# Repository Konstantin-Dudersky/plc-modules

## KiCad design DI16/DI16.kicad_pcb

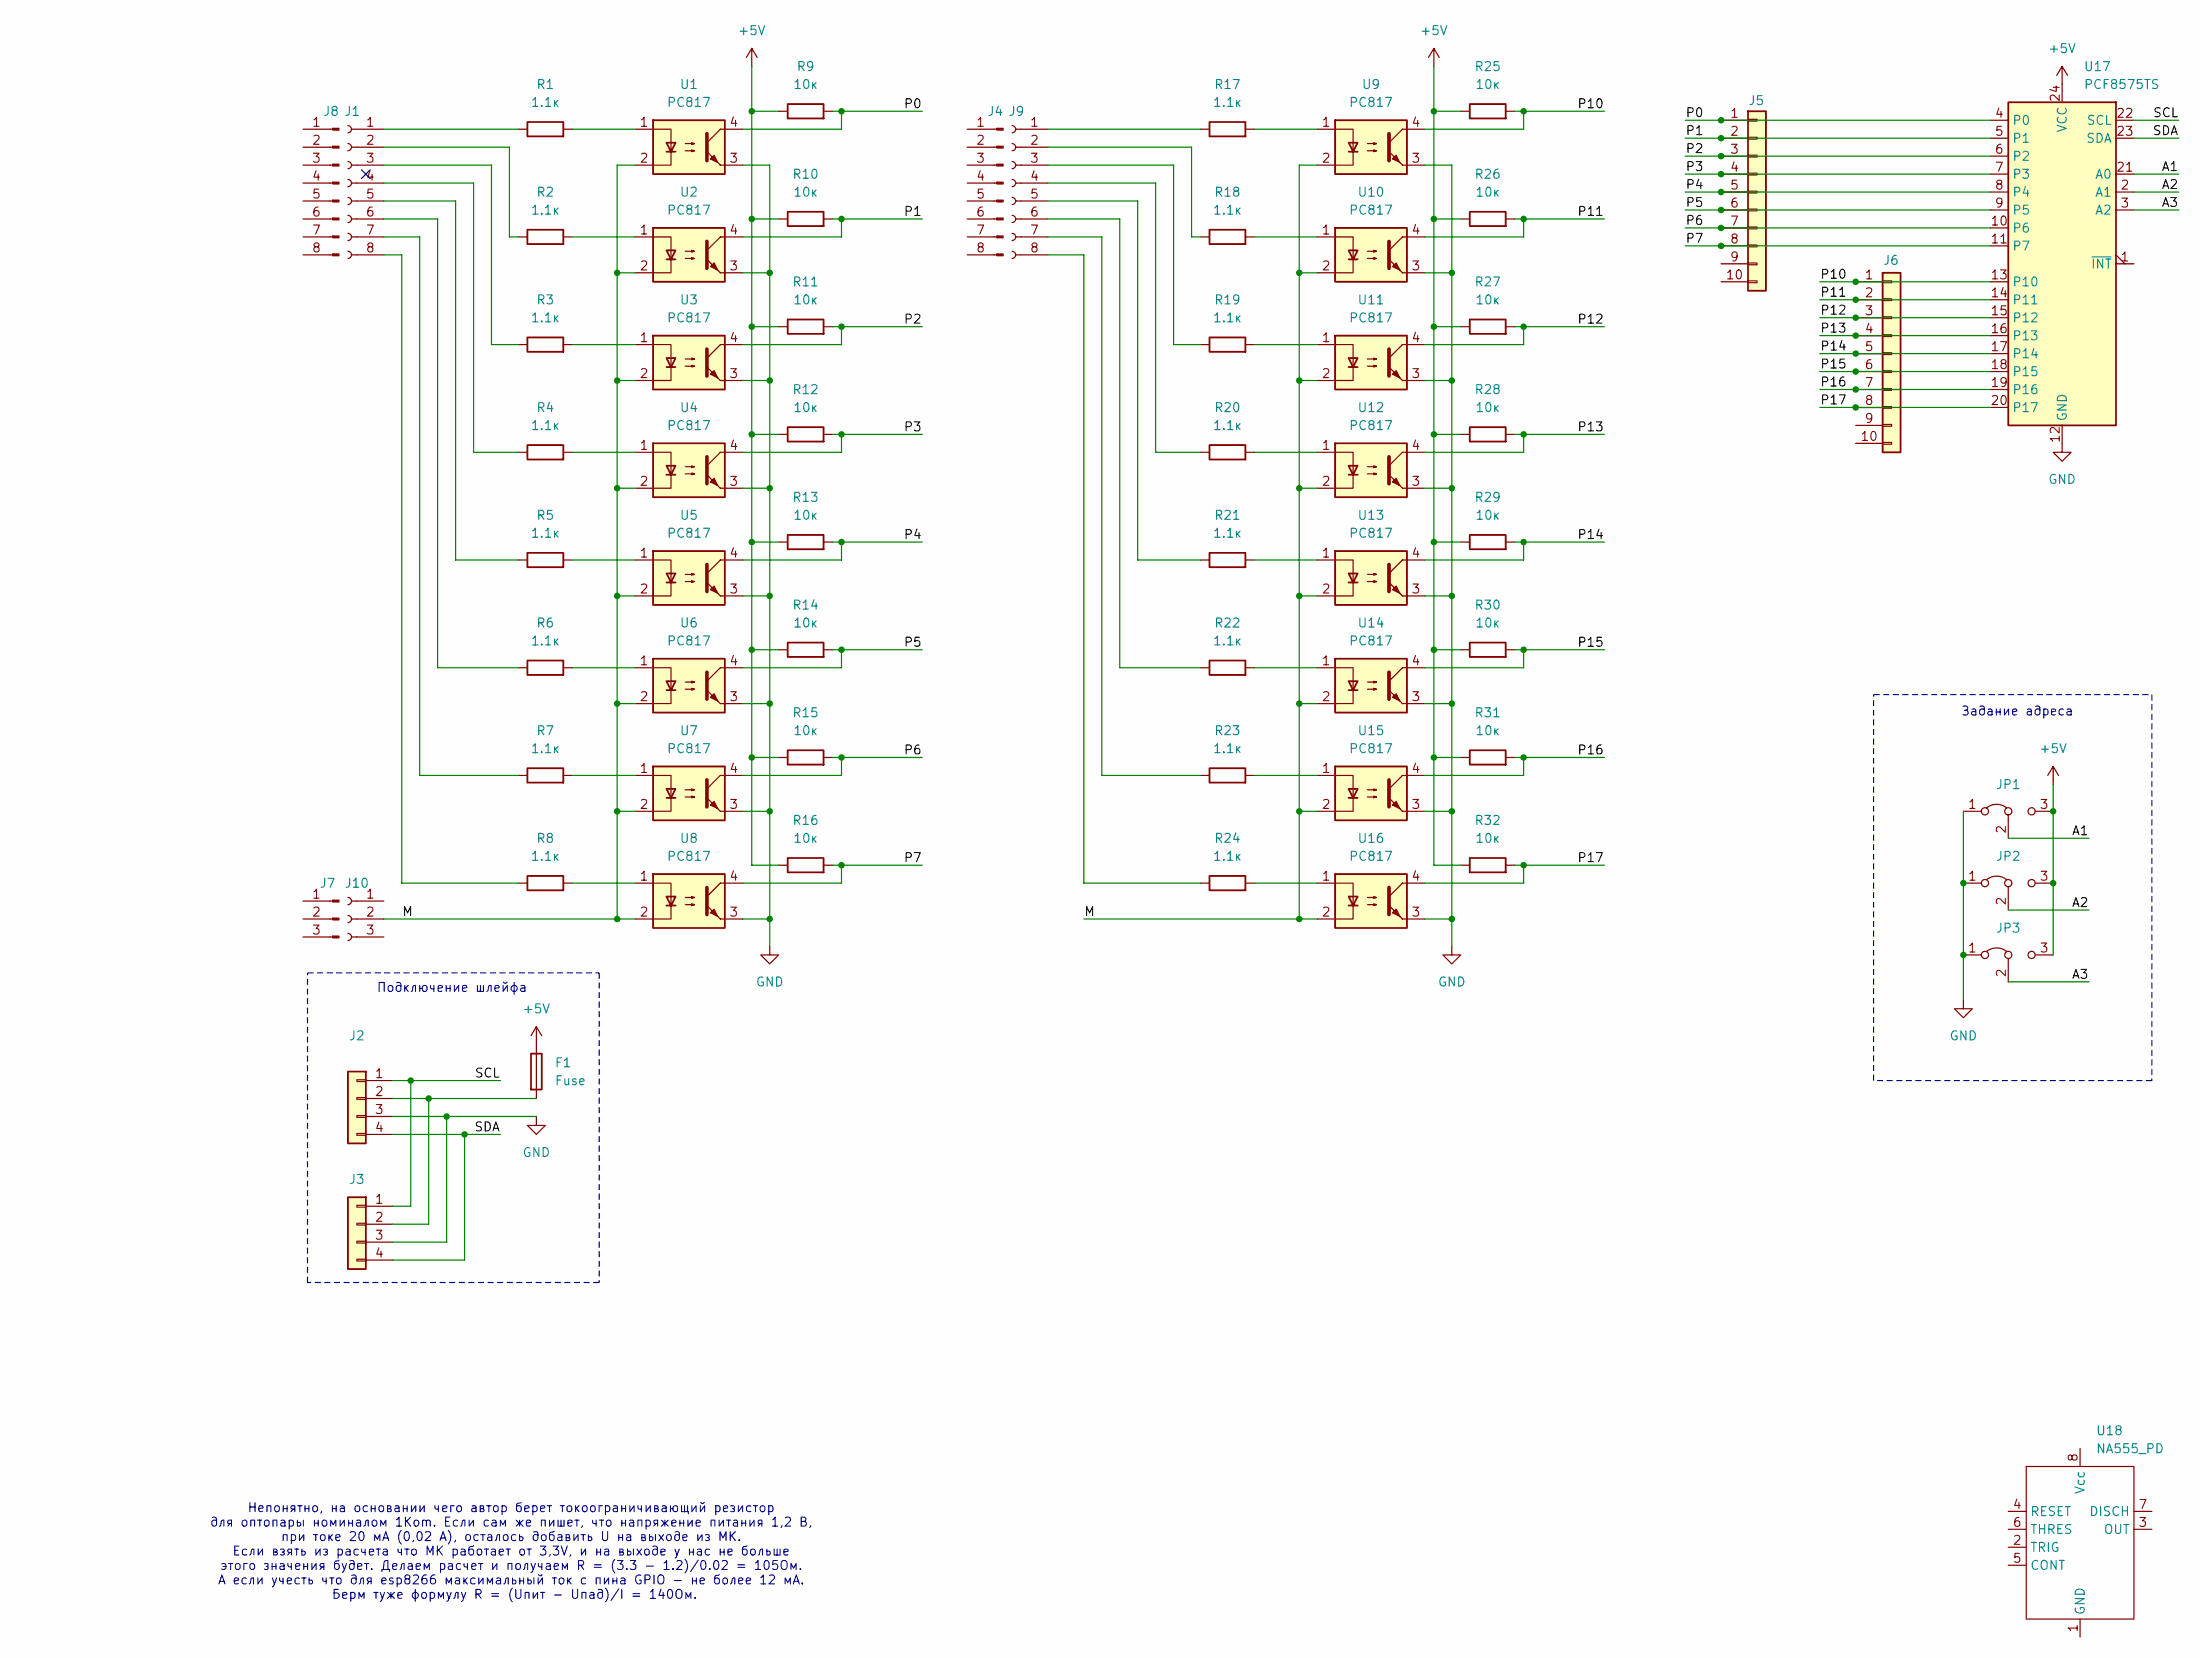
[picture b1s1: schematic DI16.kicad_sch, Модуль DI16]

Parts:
F1: Fuse; Fuseholder_Cylinder-5x20mm_Stelvio-Kontek_PTF78_Horizontal_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
J1, J9: Terminal_01x08_Socket; TerminalBlock_Phoenix_MKDS-1,5-8-5.08_1x08_P5.08mm_Horizont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
J2, J3: PinHeader_01x04_angle; PinHeader_1x04_P2.54mm_Horizontal
J4, J8: Conn_01x08_Pin
J5, J6: Conn_01x10; PinHeader_1x10_P2.54mm_Vertical
J7: Conn_01x03_Pin
J10: Conn_01x03_Socket; TerminalBlock_Phoenix_MKDS-1,5-3-5.08_1x03_P5.08mm_Horizont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
JP1, JP2, JP3: Jumper_3_Bridged12; PinHeader_1x03_P2.54mm_Vertical
R1, R2, R3, R4, R5, R6, R7, R8, R17, R18, R19, R20, R21, R22, R23, R24: 1.1к; R_Axial_DIN0309_L9.0mm_D3.2mm_P5.08mm_Vertical
R9, R10, R11, R12, R13, R14, R15, R16, R25, R26, R27, R28, R29, R30, R31, R32: 10к; R_Axial_DIN0207_L6.3mm_D2.5mm_P5.08mm_Vertical
U1, U2, U3, U4, U5, U6, U7, U8, U9, U10, U11, U12, U13, U14, U15, U16: PC817; DIP-4_W7.62mm
U17: PCF8575TS; SSOP-24_5.3x8.2mm_P0.65mm
U18: NA555_PD; DIP-8_W7.62mm_LongPads

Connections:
+5V: F1.1, JP1.3 (B), JP2.3 (B), JP3.3 (B), R9.1, R10.1, R11.1, R12.1, R13.1, R14.1, R15.1, R16.1, R25.1, R26.1, R27.1, R28.1, R29.1, R30.1, R31.1, R32.1, U17.24 (VCC)
/A1: JP1.2 (C), U17.21 (A0)
/A2: JP2.2 (C), U17.2 (A1)
/A3: JP3.2 (C), U17.3 (A2)
/M: J10.2, U1.2, U2.2, U3.2, U4.2, U5.2, U6.2, U7.2, U8.2, U9.2, U10.2, U11.2, U12.2, U13.2, U14.2, U15.2, U16.2
/P0: J5.1, R9.2, U1.4, U17.4 (P0)
/P1: J5.2, R10.2, U2.4, U17.5 (P1)
/P2: J5.3, R11.2, U3.4, U17.6 (P2)
/P3: J5.4, R12.2, U4.4, U17.7 (P3)
/P4: J5.5, R13.2, U5.4, U17.8 (P4)
/P5: J5.6, R14.2, U6.4, U17.9 (P5)
/P6: J5.7, R15.2, U7.4, U17.10 (P6)
/P7: J5.8, R16.2, U8.4, U17.11 (P7)
/P10: J6.1, R25.2, U9.4, U17.13 (P10)
/P11: J6.2, R26.2, U10.4, U17.14 (P11)
/P12: J6.3, R27.2, U11.4, U17.15 (P12)
/P13: J6.4, R28.2, U12.4, U17.16 (P13)
/P14: J6.5, R29.2, U13.4, U17.17 (P14)
/P15: J6.6, R30.2, U14.4, U17.18 (P15)
/P16: J6.7, R31.2, U15.4, U17.19 (P16)
/P17: J6.8, R32.2, U16.4, U17.20 (P17)
/SCL: J2.1, J3.1, U17.22 (SCL)
/SDA: J2.4, J3.4, U17.23 (SDA)
GND: J2.3, J3.3, JP1.1 (A), JP2.1 (A), JP3.1 (A), U1.3, U2.3, U3.3, U4.3, U5.3, U6.3, U7.3, U8.3, U9.3, U10.3, U11.3, U12.3, U13.3, U14.3, U15.3, U16.3, U17.12 (GND)
unnamed: J1.1, R1.1
unnamed: J1.2, R2.1
unnamed: J1.3, R3.1
unnamed: J1.4, R4.1
unnamed: J1.5, R5.1
unnamed: J1.6, R6.1
unnamed: J1.7, R7.1
unnamed: J1.8, R8.1
unnamed: F1.2, J2.2, J3.2
unnamed: J9.1, R17.1
unnamed: J9.2, R18.1
unnamed: J9.3, R19.1
unnamed: J9.4, R20.1
unnamed: J9.5, R21.1
unnamed: J9.6, R22.1
unnamed: J9.7, R23.1
unnamed: J9.8, R24.1
unnamed: R1.2, U1.1
unnamed: R2.2, U2.1
unnamed: R3.2, U3.1
unnamed: R4.2, U4.1
unnamed: R5.2, U5.1
unnamed: R6.2, U6.1
unnamed: R7.2, U7.1
unnamed: R8.2, U8.1
unnamed: R17.2, U9.1
unnamed: R18.2, U10.1
unnamed: R19.2, U11.1
unnamed: R20.2, U12.1
unnamed: R21.2, U13.1
unnamed: R22.2, U14.1
unnamed: R23.2, U15.1
unnamed: R24.2, U16.1

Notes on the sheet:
Непонятно, на основании чего автор берет токоограничивающий резистор для оптопары номиналом 1Kom. Если сам же пишет, что напряжение питания 1,2 В, при токе 20 мА (0,02 А), осталось добавить U на выходе из МК. Если взять из расчета что МК работает от 3,3V, и на выходе у нас не больше этого значения 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
Задание адреса
Подключение шлейфа

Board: 2 copper layers, 60 parts (0 on the bottom side), 57 nets, no tracks yet.

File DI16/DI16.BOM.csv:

"Reference","Value","Datasheet","Footprint","Qty","DNP","Стоимость"
"F1","Fuse","https://www.chipdip.by/product/fh-102","Fuse:Fuseholder_Cylinder-5x20mm_Stelvio-Kontek_PTF78_Horizontal_Open","1","","1.35"
"J1,J9","Terminal_01x08_Socket","https://www.chipdip.by/product0/8000151691","TerminalBlock_Phoenix:TerminalBlock_Phoenix_MKDS-1,5-8-5.08_1x08_P5.08mm_Horizontal","2","","2.05"
"J2,J3","PinHeader_01x04_angle","https://www.belchip.by/product/?selected_product=54121","Connector_PinHeader_2.54mm:PinHeader_1x04_P2.54mm_Horizontal","2","","0.17"
"J4,J8","Conn_01x08_Pin","https://www.chipdip.by/product/2edgk-5.08-08p","","2","","5.1"
"J5,J6","Conn_01x10","~","Connector_PinHeader_2.54mm:PinHeader_1x10_P2.54mm_Vertical","2","",""
"J7","Conn_01x03_Pin","https://www.chipdip.by/product/2edgk-5.08-03p-14-00ah","","1","","1.95"
"J10","Conn_01x03_Socket","https://www.chipdip.by/product/2edgr-5.08-03p","TerminalBlock_Phoenix:TerminalBlock_Phoenix_MKDS-1,5-3-5.08_1x03_P5.08mm_Horizontal","1","","0.78"
"R1,R2,R3,R4,R5,R6,R7,R8,R17,R18,R19,R20,R21,R22,R23,R24","1.1к","https://www.chipdip.by/product0/63157","Resistor_THT:R_Axial_DIN0309_L9.0mm_D3.2mm_P5.08mm_Vertical","16","","0.11"
"R9,R10,R11,R12,R13,R14,R15,R16,R25,R26,R27,R28,R29,R30,R31,R32","10к","https://www.chipdip.by/product0/48560","Resistor_THT:R_Axial_DIN0207_L6.3mm_D2.5mm_P5.08mm_Vertical","16","","0.07"
"U1,U2,U3,U4,U5,U6,U7,U8,U9,U10,U11,U12,U13,U14,U15,U16","PC817","https://www.chipdip.by/product/fod817b","Package_DIP:DIP-4_W7.62mm","16","","2.25"
"U17","PCF8575TS","https://www.chipdip.by/product0/8153866596","Package_SO:SSOP-24_5.3x8.2mm_P0.65mm","1","","14.5"

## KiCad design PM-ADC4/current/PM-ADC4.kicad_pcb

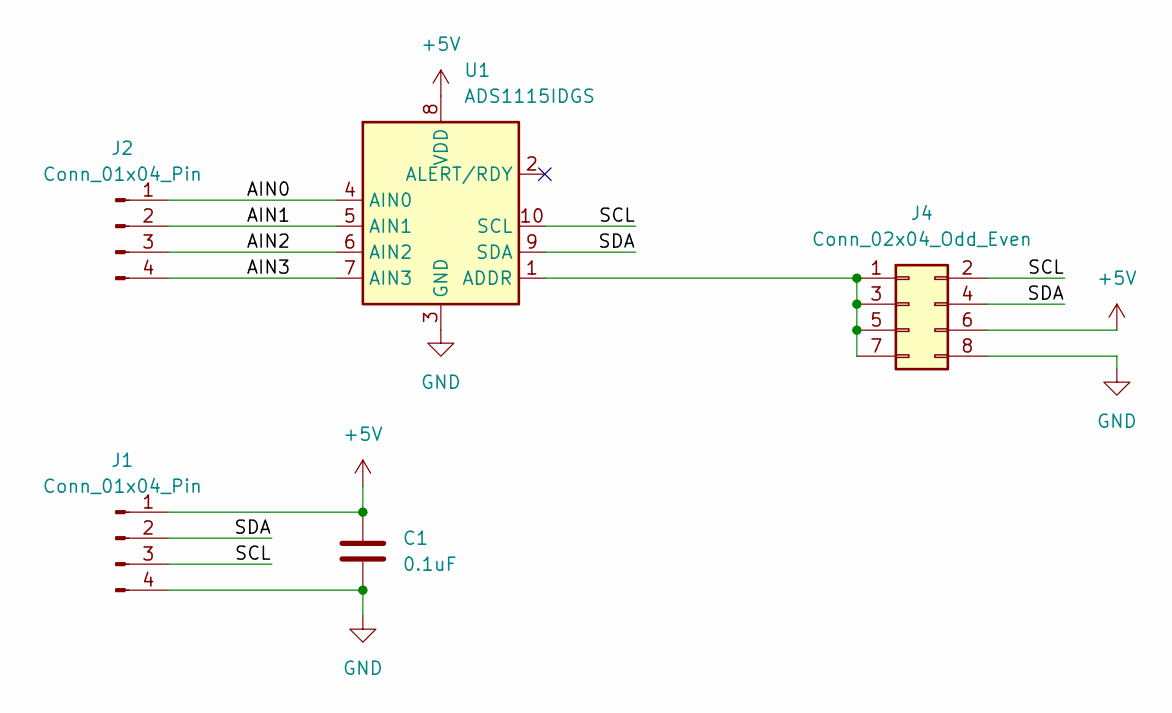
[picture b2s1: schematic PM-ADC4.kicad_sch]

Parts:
C1: 0.1uF; C_1206_3216Metric_Pad1.33x1.80mm_HandSolder
J1, J2: Conn_01x04_Pin; PinHeader_1x04_P2.54mm_Vertical_SMD_Pin1Left
J4: Conn_02x04_Odd_Even; PinHeader_2x04_P2.54mm_Vertical_SMD
U1: ADS1115IDGS; VSSOP-10_3x3mm_P0.5mm

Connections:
+5V: C1.1, J1.1, J4.6, U1.8 (VDD)
/AIN0: J2.1, U1.4 (AIN0)
/AIN1: J2.2, U1.5 (AIN1)
/AIN2: J2.3, U1.6 (AIN2)
/AIN3: J2.4, U1.7 (AIN3)
/SCL: J1.3, J4.2, U1.10 (SCL)
/SDA: J1.2, J4.4, U1.9 (SDA)
GND: C1.2, J1.4, J4.8, U1.3 (GND)
unnamed: J4.1, J4.3, J4.5, J4.7, U1.1 (ADDR)

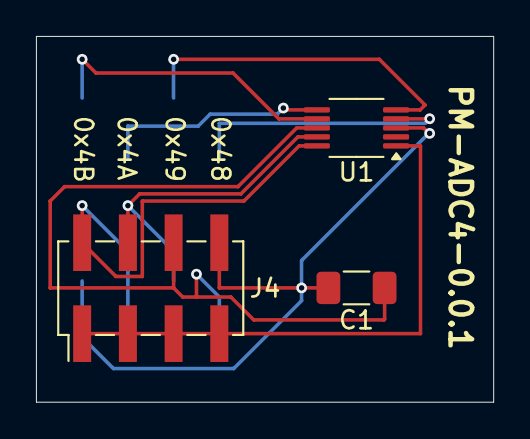
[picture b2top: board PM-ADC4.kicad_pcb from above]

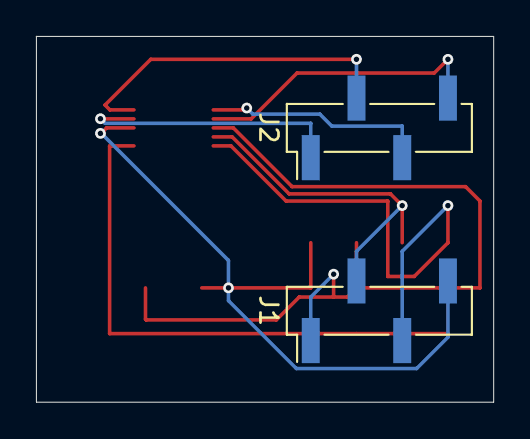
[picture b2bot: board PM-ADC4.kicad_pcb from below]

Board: 2 copper layers, 25.4 x 20.3 mm, 5 parts (2 on the bottom side), 9 nets.

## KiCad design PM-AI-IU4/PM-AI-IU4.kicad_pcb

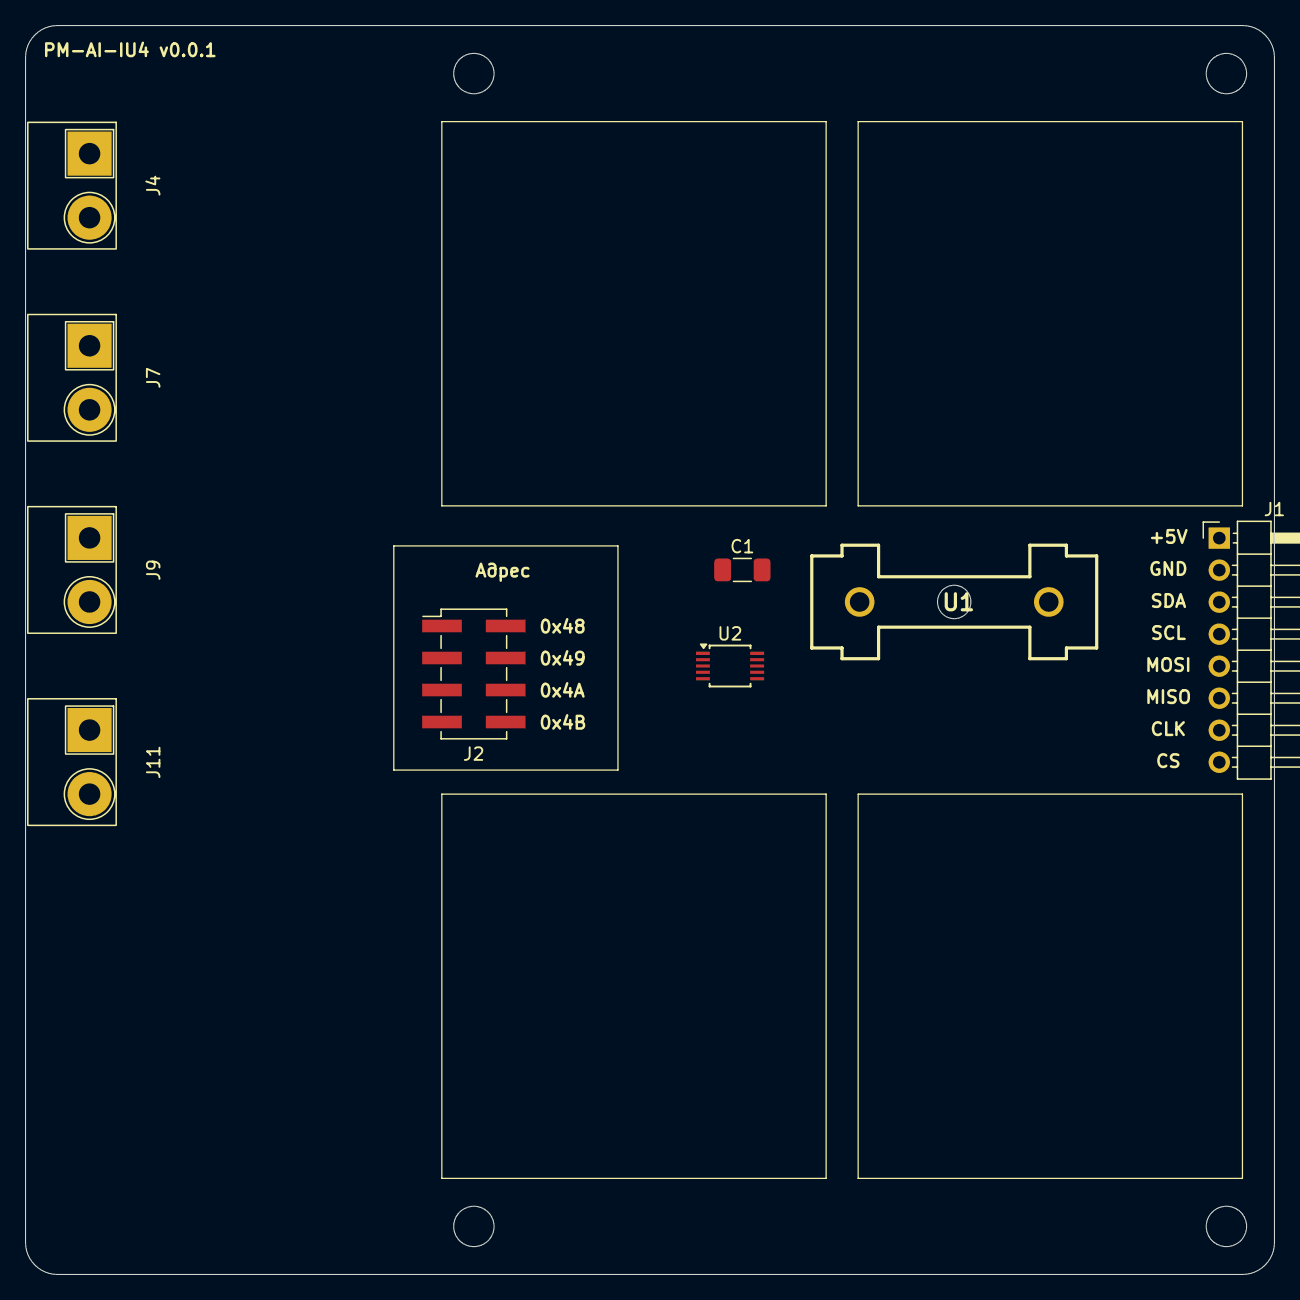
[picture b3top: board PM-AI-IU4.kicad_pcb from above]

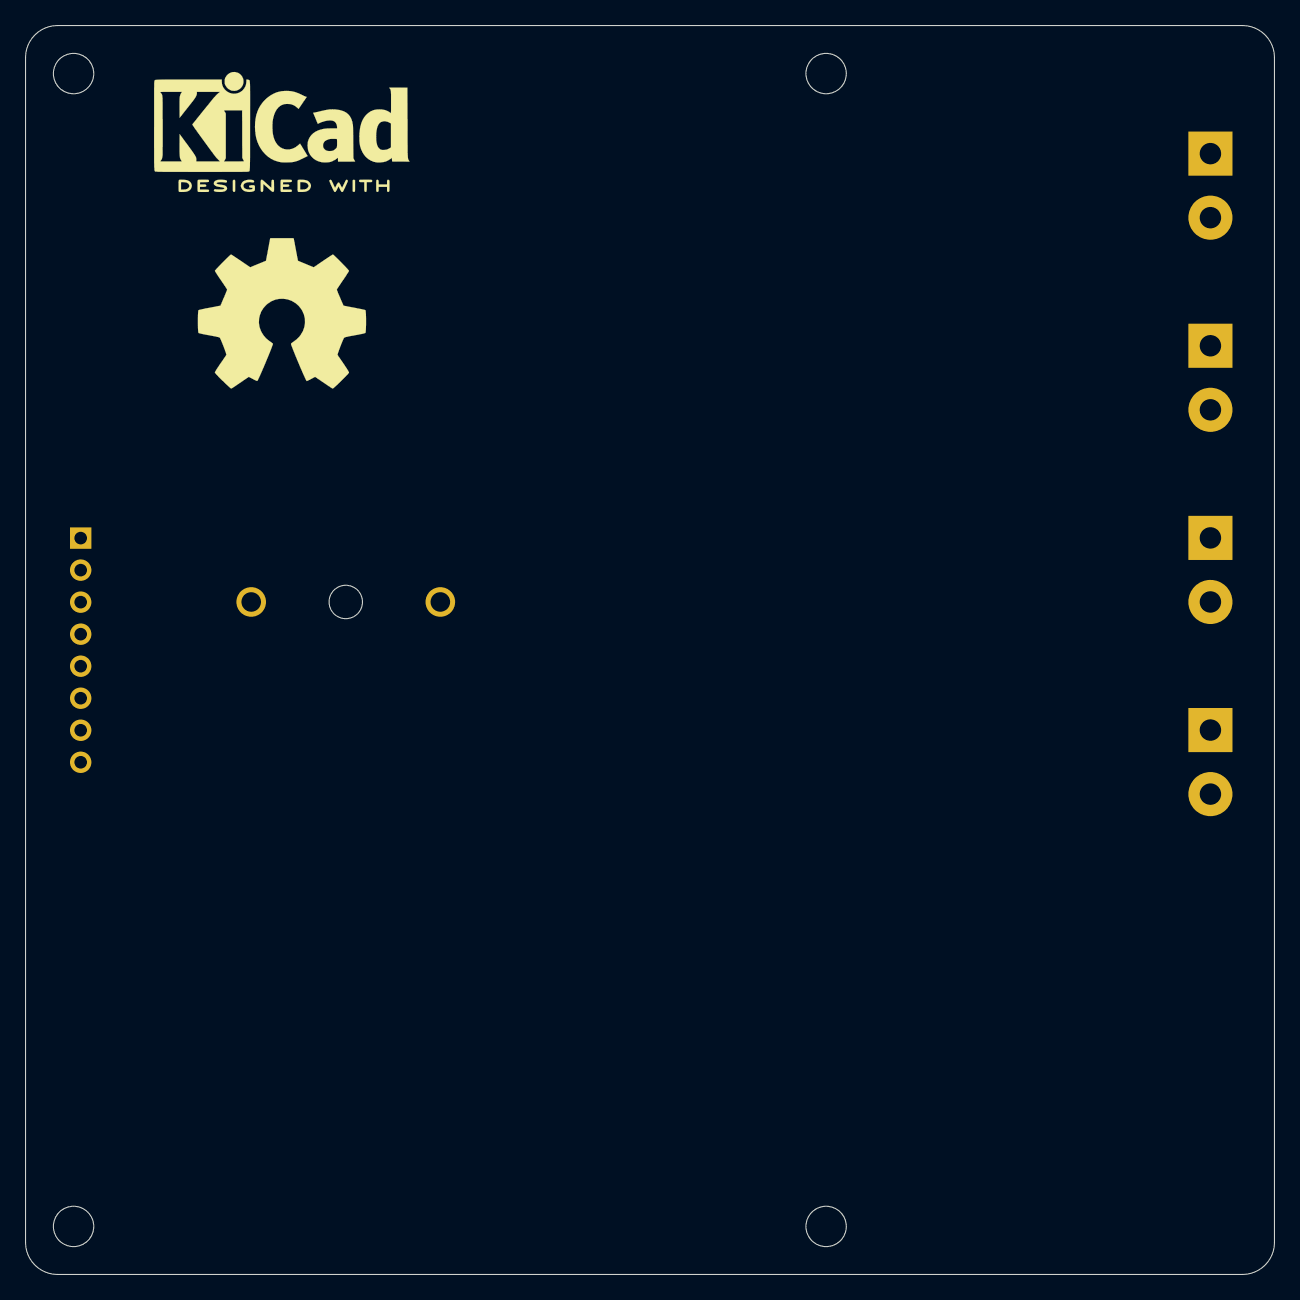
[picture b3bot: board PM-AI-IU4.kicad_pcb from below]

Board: 2 copper layers, 99.1 x 99.1 mm, 15 parts (2 on the bottom side), 6 nets, no tracks yet.

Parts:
C1: 100nF 1206; C_1206_3216Metric_Pad1.33x1.80mm_HandSolder
H1, H2, H3, H4: MountingHole; MountingHole_3.2mm_M3
J1: PinHeader P2.54 01x08 THT Angle; PinHeader_1x08_P2.54mm_Horizontal
J2: PinHeader P2.54 02x04 SMD Straight; PinHeader_2x04_P2.54mm_Vertical_SMD
J4, J7, J9, J11: 2EDGR-5.08-02P; Degson_2EDGR-5.08-02P
U1: 64900001039; Fuseholder
U2: ADS1115; TSSOP-10_3x3mm_P0.5mm
logo_kicad: KiCad-Logo2_8mm_SilkScreen
logo_oshw: OSHW-Symbol_13.4x12mm_SilkScreen

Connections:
/ADDR: J2.2, J2.4, J2.6, J2.8, U2.1 (ADDR)
/SCL: J1.4, J2.7, U2.10 (SCL)
/SDA: J1.3, J2.5, U2.9 (SDA)
GND: C1.2, J1.2, J2.1, J4.2, J7.2, J9.2, J11.2, U2.3 (GND)
unnamed: J1.1, U1.2
VDD: C1.1, J2.3, U1.1, U2.8 (VDD)

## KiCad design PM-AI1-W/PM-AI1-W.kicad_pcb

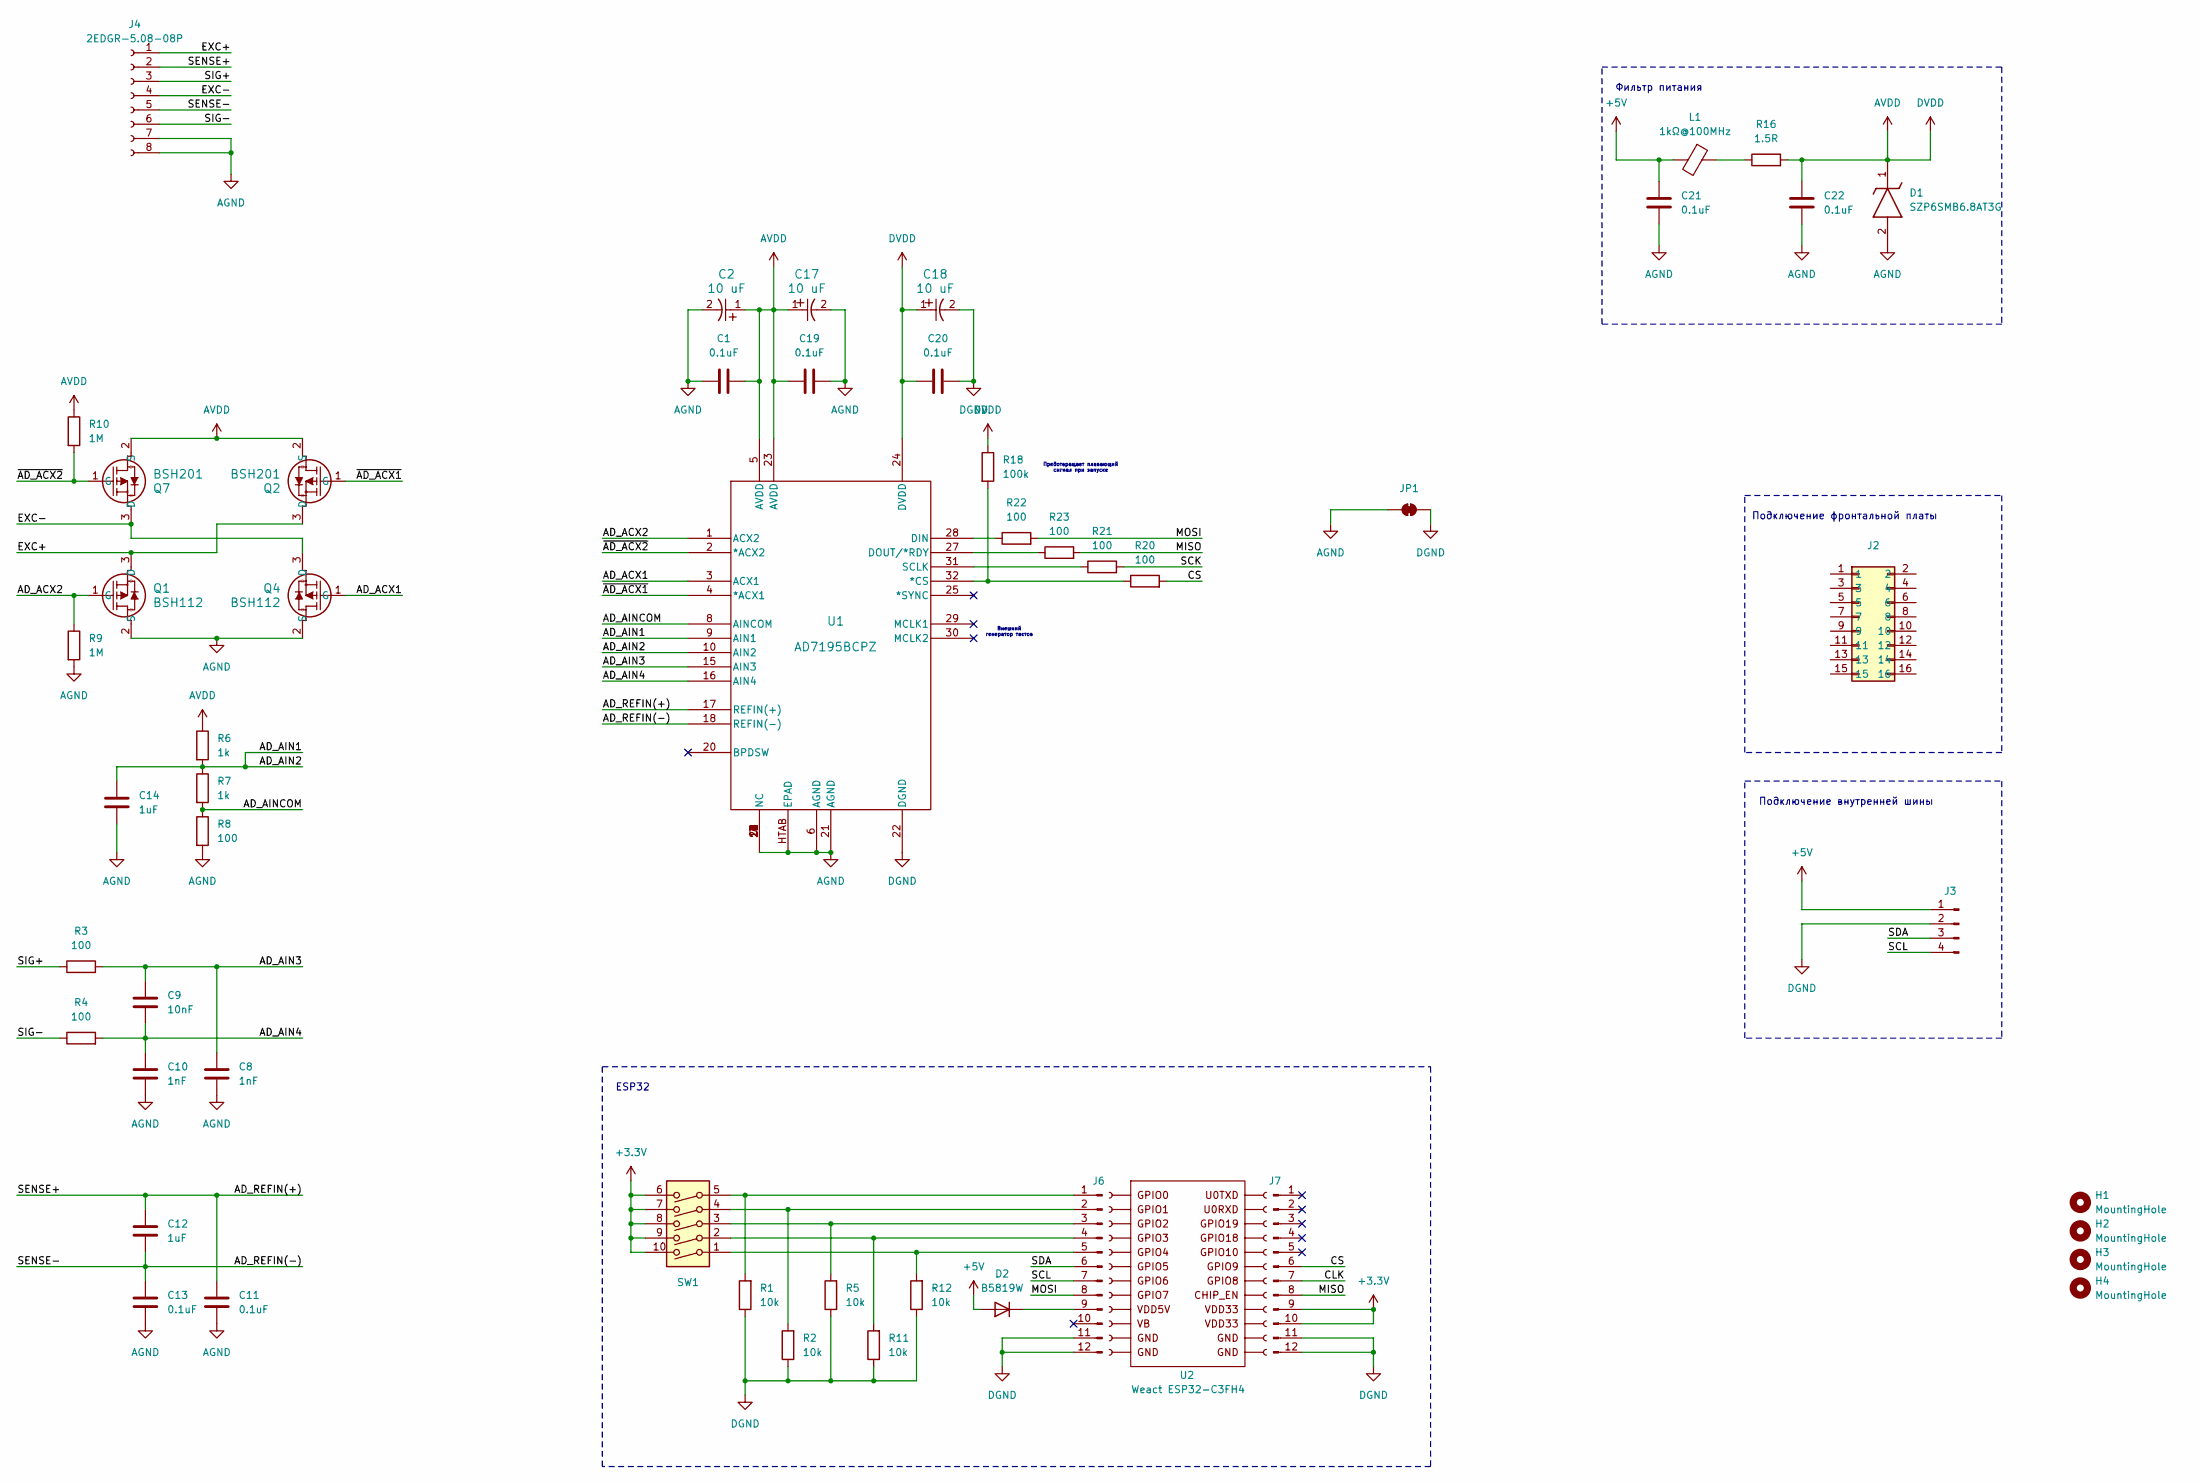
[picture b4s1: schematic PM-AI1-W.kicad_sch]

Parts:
C1, C11, C13, C19, C20, C21, C22: 0.1uF; C_1206_3216Metric_Pad1.33x1.80mm_HandSolder; part_ipn C_100nF_1206
C2, C17, C18: 10 uF; TAJA_AVX-M; part_ipn TAJA106M016RNJ
C8, C10: 1nF; C_1206_3216Metric_Pad1.33x1.80mm_HandSolder; part_ipn C_1nF_1206
C9: 10nF; C_1206_3216Metric_Pad1.33x1.80mm_HandSolder; part_ipn C_10nF_1206
C12, C14: 1uF; C_1206_3216Metric_Pad1.33x1.80mm_HandSolder; part_ipn C_1uF_1206
D1: SZP6SMB6.8AT3G; DIOM5436X247N; Manufacturer_Part_Number SZP6SMB6.8AT3G; Mouser Part Number 863-SZP6SMB6.8AT3G
D2: B5819W; D_SOD-123; part_ipn B5819W
H1, H2, H3, H4: MountingHole; MountingHole_3.2mm_M3
J2: PM-front-02x08
J3: Conn_01x04_Pin; PinHeader_1x04_P2.54mm_Horizontal; part_ipn PinHeader P2.54 01x04 THT Angle
J4: 2EDGR-5.08-08P; Degson_2EDGR-5.08-08P; part_ipn 2EDGR-5.08-08P
J6, J7: PinHeader_01x12_P2.54_THT_straight; PinHeader_1x12_P2.54mm_Vertical; part_ipn PinHeader_01x12_P2.54_THT_straight
JP1: SolderJumper_2_Bridged; SolderJumper-2_P1.3mm_Bridged_RoundedPad1.0x1.5mm
L1: 1kΩ@100MHz; L_1206_3216Metric_Pad1.42x1.75mm_HandSolder; part_ipn FB_300mΩ_1kΩ@100MHz_1206
Q1, Q4: BSH112; SOT23_NEX-M; part_ipn BSH112
Q2, Q7: BSH201; SOT23_NEX-M; part_ipn BSH201
R1, R2, R5, R11, R12: 10k; R_1206_3216Metric_Pad1.30x1.75mm_HandSolder; part_ipn R_10k_1206_1%
R3, R4, R8, R20, R21, R22, R23: 100; R_1206_3216Metric_Pad1.30x1.75mm_HandSolder; part_ipn R_100_1206_1%
R6, R7: 1k; R_1206_3216Metric_Pad1.30x1.75mm_HandSolder; part_ipn R_1k_1206_1%
R9, R10: 1M; R_1206_3216Metric_Pad1.30x1.75mm_HandSolder; part_ipn R_1M_1206_1%
R16: 1.5R; R_1206_3216Metric_Pad1.30x1.75mm_HandSolder; part_ipn R_1.5R_1206_1%
R18: 100k; R_1206_3216Metric_Pad1.30x1.75mm_HandSolder; part_ipn R_100k_1206_1%
SW1: DSIC05LS-P; part_ipn DSIC05LS-P
U1: AD7195BCPZ
U2: Weact ESP32-C3FH4; part_ipn Weact ESP32-C3FH4

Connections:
+3.3V: J7.9, J7.10, SW1.6, SW1.7, SW1.8, SW1.9, SW1.10
+5V: C21.2, D2.2 (A), J3.1, L1.2
/AD_ACX1: Q4.1 (G), U1.3 (ACX1)
/AD_ACX2: Q1.1 (G), R9.1, U1.1 (ACX2)
/AD_AIN1: C14.1, R6.2, R7.1, U1.9 (AIN1), U1.10 (AIN2)
/AD_AIN3: C8.1, C9.1, R3.2, U1.15 (AIN3)
/AD_AIN4: C9.2, C10.1, R4.2, U1.16 (AIN4)
/AD_AINCOM: R7.2, R8.1, U1.8 (AINCOM)
/AD_REFIN(+): C11.2, C12.1, J4.2, U1.17 (REFIN(+))
/AD_REFIN(-): C12.2, C13.2, J4.5, U1.18 (REFIN(-))
/CLK: J7.7
/CS: J7.6, R20.2
/EXC+: J4.1, Q1.3 (D), Q2.3 (D)
/EXC-: J4.4, Q4.3 (D), Q7.3 (D)
/MISO: J7.8, R23.2
/MOSI: J6.8, R22.2
/SCK: R21.2
/SCL: J3.4, J6.7
/SDA: J3.3, J6.6
/SIG+: J4.3, R3.1
/SIG-: J4.6, R4.1
/~AD_ACX1: Q2.1 (G), U1.4 (*ACX1)
/~AD_ACX2: Q7.1 (G), R10.2, U1.2 (*ACX2)
AGND: C1.1, C2.2, C8.2, C10.2, C11.1, C13.1, C14.2, C17.2, C19.2, C21.1, C22.1, D1.2 (A), J4.7, J4.8, JP1.1 (A), Q1.2 (S), Q4.2 (S), R8.2, R9.2, U1.6 (AGND), U1.7 (NC), U1.11 (NC), U1.12 (NC), U1.13 (NC), U1.14 (NC), U1.19 (NC), U1.21 (AGND), U1.26 (NC), U1.HTAB (EPAD)
AVDD: C1.2, C2.1, C17.1, C18.1, C19.1, C20.1, C22.2, D1.1 (K), Q2.2 (S), Q7.2 (S), R6.1, R10.1, R16.2, R18.1, U1.5 (AVDD), U1.23 (AVDD), U1.24 (DVDD)
DGND: C18.2, C20.2, J3.2, J6.11, J6.12, J7.11, J7.12, JP1.2 (B), R1.1, R2.1, R5.1, R11.1, R12.1, U1.22 (DGND)
unnamed: D2.1 (K), J6.9
unnamed: J6.1, R1.2, SW1.5
unnamed: J6.2, R2.2, SW1.4
unnamed: J6.3, R5.2, SW1.3
unnamed: J6.4, R11.2, SW1.2
unnamed: J6.5, R12.2, SW1.1
unnamed: L1.1, R16.1
unnamed: R18.2, R20.1, U1.32 (*CS)
unnamed: R22.1, U1.28 (DIN)
unnamed: R23.1, U1.27 (DOUT/*RDY)
unnamed: R21.1, U1.31 (SCLK)

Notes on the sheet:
Внешний генератор тактов
Предотвращает плавающий сигнал при запуске
ESP32
Подключение фронтальной платы
Подключение внутренней шины
Фильтр питания

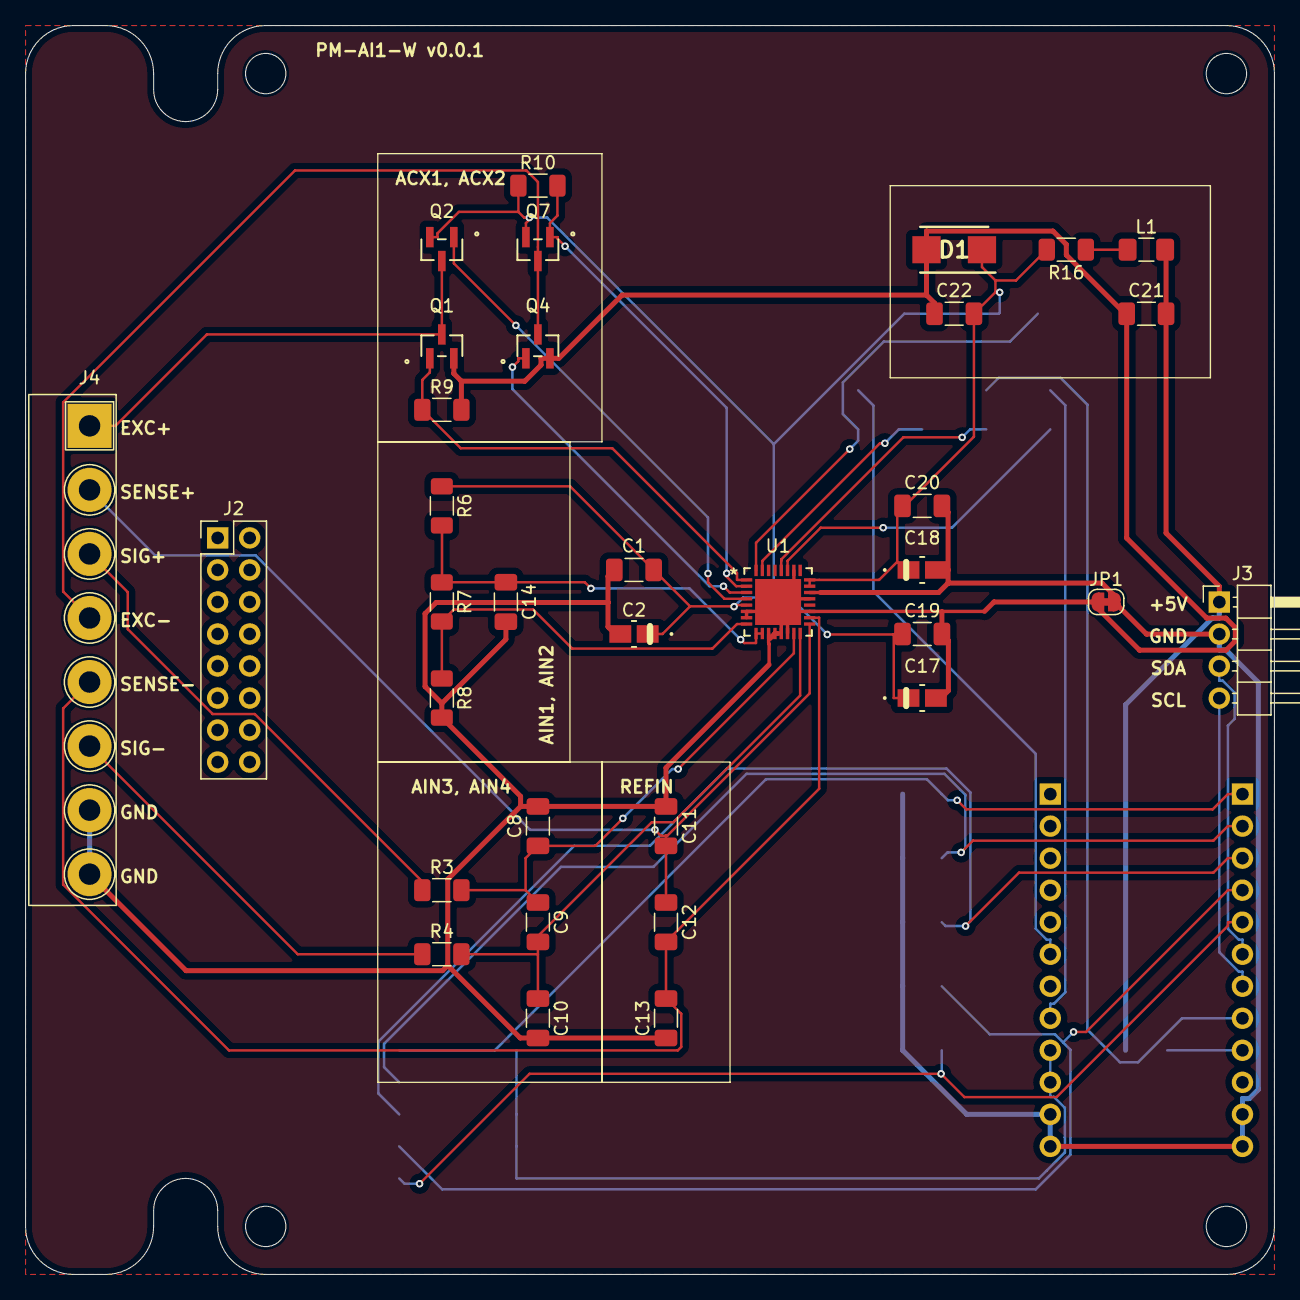
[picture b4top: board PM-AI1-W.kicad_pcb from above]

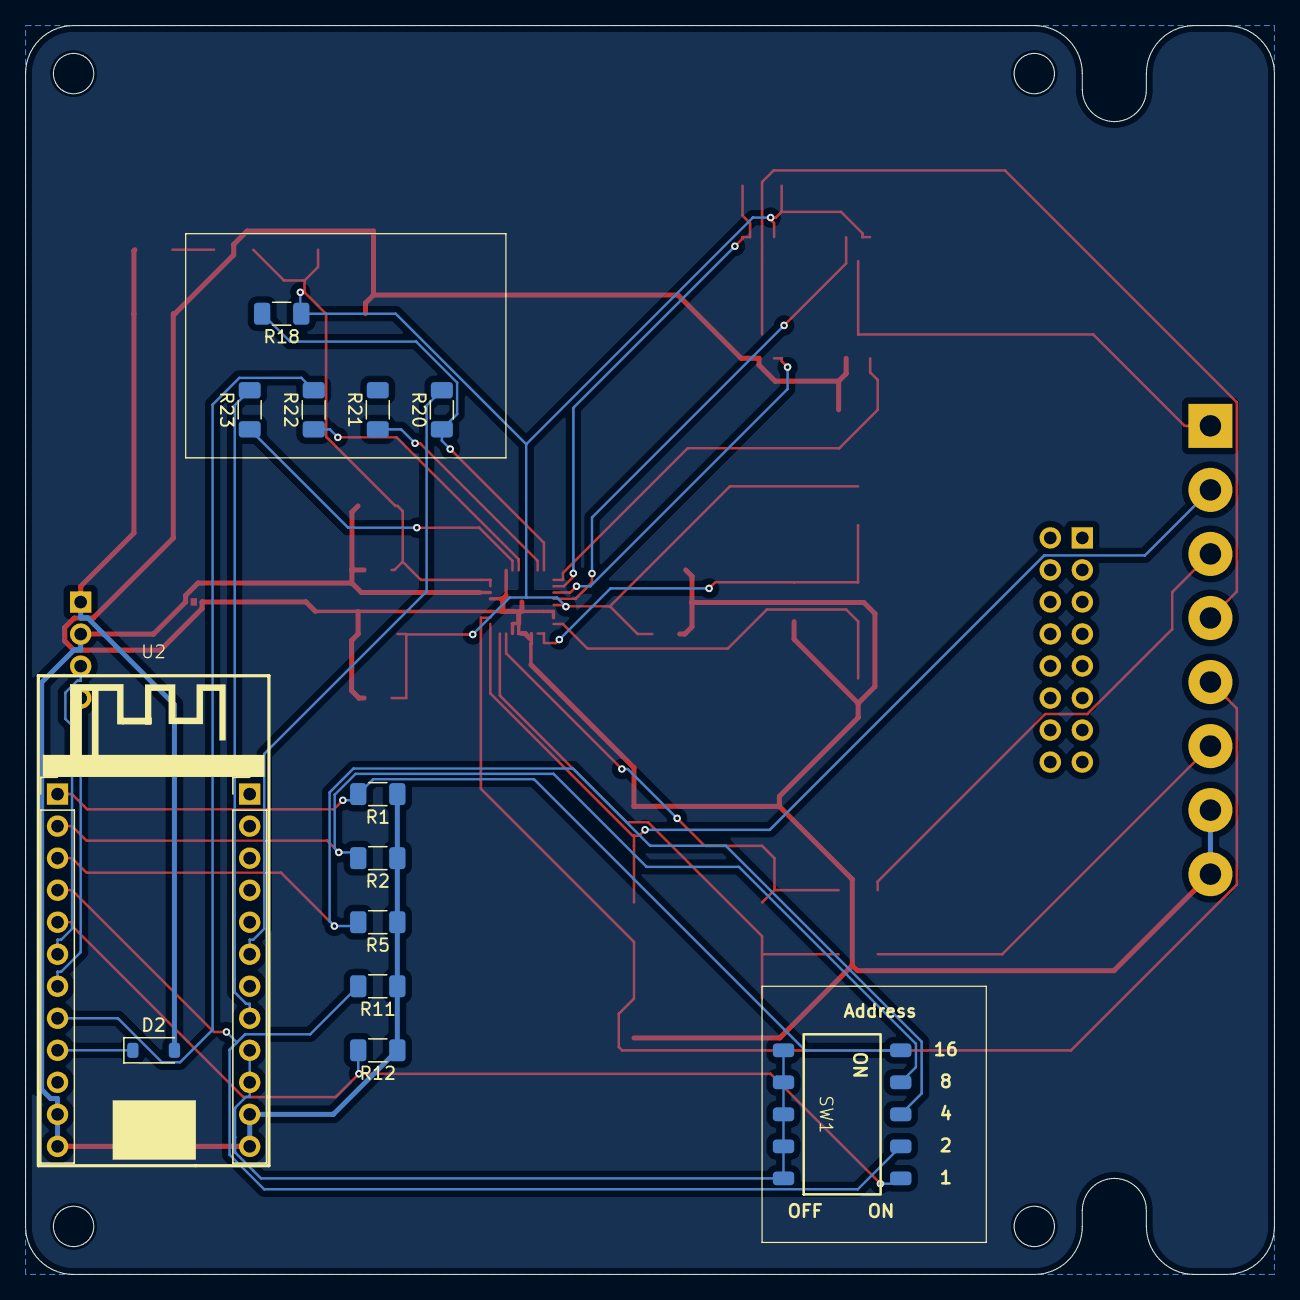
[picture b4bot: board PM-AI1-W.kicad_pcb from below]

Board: 2 copper layers, 99.1 x 99.1 mm, 53 parts (15 on the bottom side), 35 nets.
